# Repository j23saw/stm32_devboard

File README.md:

# stm32_devboard
An STM32F103 MCU based board with on-board IMU, SD card interface and USB interface.

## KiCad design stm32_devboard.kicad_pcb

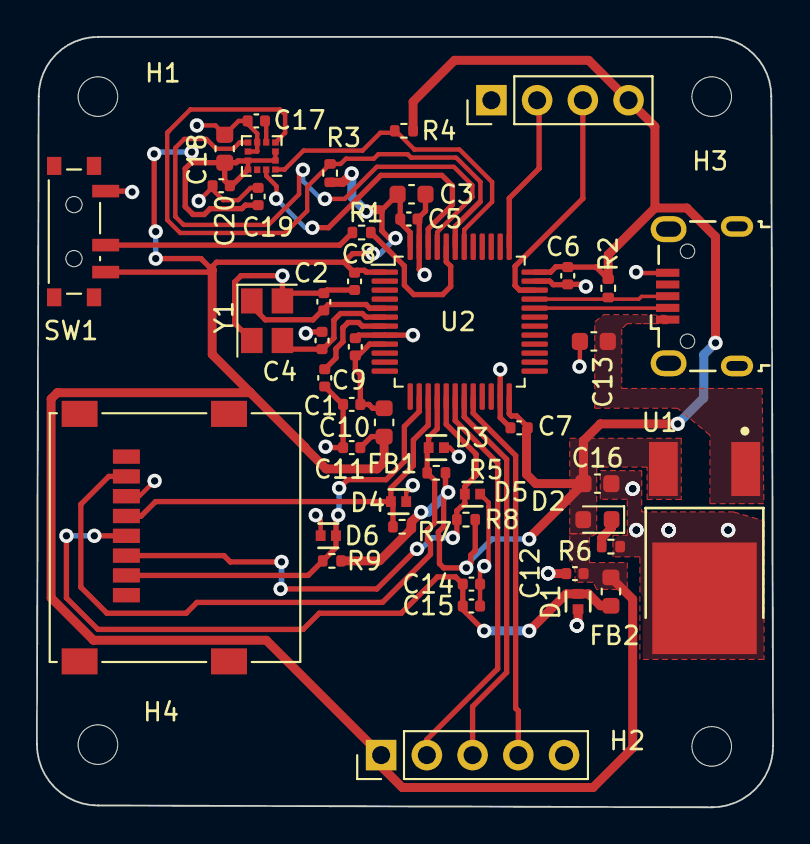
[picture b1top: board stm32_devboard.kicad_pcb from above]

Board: 2 copper layers, 40.9 x 42.8 mm, 50 parts (0 on the bottom side), 27 nets.

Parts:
C1, C5, C6, C7, C8, C9, C15, C17, C19, C20: 100n; C_0402_1005Metric
C2, C4: 10p; C_0402_1005Metric
C3, C13, C18: 10u; C_0603_1608Metric
C10, C11: 1u; C_0402_1005Metric
C12, C14: 2u2; C_0402_1005Metric
C16: 4.7u; C_0603_1608Metric
D1, D3, D4, D5, D6: SM6T12A; Semtech-SLP1006P2-0-0-MFG
D2: LED; LED_0603_1608Metric
FB1: 120R@100Hz; L_0603_1608Metric
FB2: FerriteBead; L_0603_1608Metric
H1, H2, H3, H4: MountingHole; MountingHole_2.2mm_M2
J1: Conn_01x04_Male; PinHeader_1x04_P2.54mm_Vertical
J2: USB_B_Micro; USB_Micro-B_Wuerth_629105150521
J3: Micro_SD_Card; microSD_HC_Wuerth_693072010801
J4: Conn_01x05_Male; PinHeader_1x05_P2.54mm_Vertical
R1, R5, R7, R8, R9: 10k; R_0402_1005Metric
R2, R3, R4, R6: 1k5; R_0402_1005Metric
SW1: SW_SPDT; SW_SPDT_PCM12
U1: NCP5501DT33RKG; ON_Semi-CASE_369C-0-0-0
U2: STM32F103CBT6; LQFP-48_7x7mm_P0.5mm
U3: LSM303C; LGA-12_2x2mm_P0.5mm
Y1: Crystal_GND24; Crystal_SMD_3225-4Pin_3.2x2.5mm

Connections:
+3.3VA: C9.1, C10.1, FB1.1, U2.9 (VDDA)
+3V3: C3.2, C5.1, C6.1, C7.1, C8.1, C11.1, C12.1, C16.1, C18.1, C19.1, C20.1, D2.2 (A), FB1.2, FB2.1, J1.4, J4.1, R2.1, R3.1, R4.1, R5.1, R7.1, R8.1, R9.1, SW1.3 (C), U1.3 (Vout), U2.1 (VBAT), U2.24 (VDD), U2.36 (VDD), U2.48 (VDD), U3.2 (CS_XL), U3.3 (CS_MAG), U3.9 (VDD), U3.10 (VDDIO)
/BOOT0: R1.2, U2.44 (BOOT0)
/GPIO_1: J4.2, U2.18 (PB0)
/GPIO_2: J4.3, U2.19 (PB1)
/GPIO_3: J4.4, U2.20 (PB2)
/HSE_IN: C2.1, U2.5 (PD0), Y1.1
/HSE_OUT: C4.1, U2.6 (PD1), Y1.3
/INT_MAG: U2.45 (PB8), U3.7 (INT_MAG)
/INT_XL: U2.46 (PB9), U3.12 (INT_XL)
/NRST: C1.1, U2.7 (NRST)
/PWR_LED: D2.1 (K), R6.2
/SD_VDD: C14.1, C15.1, D1.1 (A1), FB2.2, J3.4 (VDD)
/SWCLK: J1.2, U2.37 (PA14)
/SWDIO: J1.3, U2.34 (PA13)
/SW_BOOT0: R1.1, SW1.2 (B)
/USB_D+: J2.3 (D+), R2.2, U2.33 (PA12)
/USB_D-: J2.2 (D-), U2.32 (PA11)
GND: C1.2, C2.2, C3.1, C4.2, C5.2, C6.2, C7.2, C8.2, C9.2, C10.2, C11.2, C12.2, C13.2, C14.2, C15.2, C16.2, C17.2, C18.2, C19.2, C20.2, D1.2 (A2), D3.2 (A2), D4.2 (A2), D5.2 (A2), D6.2 (A2), J1.1, J2.5 (GND), J3.6 (VSS), J4.5, R6.1, SW1.1 (A), U1.TAB (GND), U2.8 (VSSA), U2.23 (VSS), U2.35 (VSS), U2.47 (VSS), U3.6 (GND), U3.8 (GND), Y1.2, Y1.4
IMU_SCL: R4.2, U2.42 (PB6), U3.1 (SCL/SPC)
IMU_SDA: R3.2, U2.43 (PB7), U3.4 (SDA/SDI/SDO)
unnamed: C17.1, U3.5 (C1)
SD_MISO: D3.1 (A1), J3.7 (DAT0), R5.2, U2.16 (PA6)
SD_MOSI: D5.1 (A1), J3.3 (CMD), R8.2, U2.17 (PA7)
SD_SCK: D4.1 (A1), J3.5 (CLK), R7.2, U2.15 (PA5)
SD_SS: D6.1 (A1), J3.2 (DAT3/CD), R9.2, U2.14 (PA4)
VBUS: C13.1, J2.1 (VBUS), U1.1 (Vin)

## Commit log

2022-03-01 first
2022-03-03 sd card schematic done
2022-03-22 add imu
2022-03-25 schematic annotation
2022-04-02 layout and sch update
2022-04-02 layout done
2022-05-08 finish
